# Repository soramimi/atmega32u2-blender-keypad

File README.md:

# atmega32u2-blender-keypad

Customized keypad for modeling with Blender.

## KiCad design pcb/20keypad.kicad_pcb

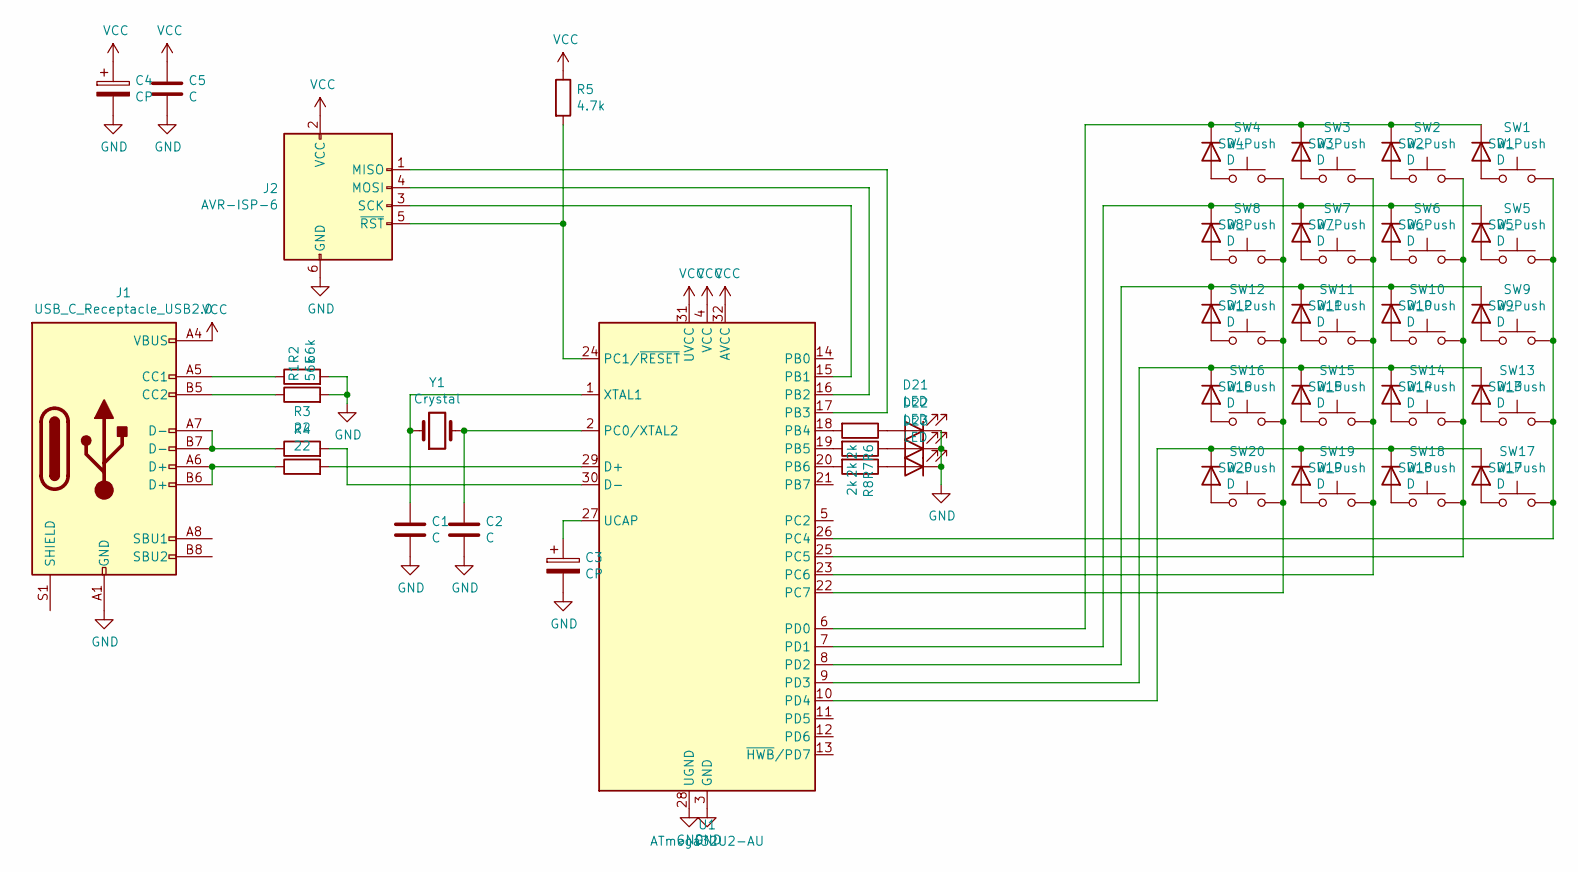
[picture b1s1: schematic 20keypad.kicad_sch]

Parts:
C1, C2, C5: C; C_Disc_D3.0mm_W1.6mm_P2.50mm
C3, C4: CP; CP_Radial_D6.3mm_P2.50mm
D1, D2, D3, D4, D5, D6, D7, D8, D9, D10, D11, D12, D13, D14, D15, D16, D17, D18, D19, D20: D; D_A-405_P7.62mm_Horizontal
D21, D22, D23: LED; LED_D3.0mm
J1: USB_C_Receptacle_USB2.0; USB_C_Receptacle_HRO_TYPE-C-31-M-12
J2: AVR-ISP-6; PinHeader_2x03_P2.54mm_Vertical
R1, R2: 56k; R_Axial_DIN0204_L3.6mm_D1.6mm_P2.54mm_Vertical
R3, R4: 22; R_Axial_DIN0204_L3.6mm_D1.6mm_P2.54mm_Vertical
R5: 4.7k; R_Axial_DIN0204_L3.6mm_D1.6mm_P2.54mm_Vertical
R6, R7, R8: 2k; R_Axial_DIN0204_L3.6mm_D1.6mm_P2.54mm_Vertical
SW1, SW2, SW3, SW4, SW5, SW6, SW7, SW8, SW9, SW10, SW11, SW12, SW13, SW14, SW15, SW16, SW17, SW18, SW19, SW20: SW_Push; SW_Cherry_MX_1.00u_PCB
U1: ATmega32U2-AU; TQFP-32_7x7mm_P0.8mm
Y1: Crystal; Crystal_HC49-U_Vertical

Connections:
GND: C1.2, C2.2, C3.2, C4.2, C5.2, D21.1 (K), D22.1 (K), D23.1 (K), J1.A1 (GND), J1.A12 (GND), J1.B1 (GND), J1.B12 (GND), J2.6 (GND), R1.2, R2.2, U1.3 (GND), U1.28 (UGND)
unnamed: C1.1, U1.1 (XTAL1), Y1.1
unnamed: C2.1, U1.2 (PC0/XTAL2), Y1.2
unnamed: C3.1, U1.27 (UCAP)
unnamed: D1.1 (K), D2.1 (K), D3.1 (K), D4.1 (K), U1.6 (PD0)
unnamed: D1.2 (A), SW1.1
unnamed: D2.2 (A), SW2.1
unnamed: D3.2 (A), SW3.1
unnamed: D4.2 (A), SW4.1
unnamed: D5.1 (K), D6.1 (K), D7.1 (K), D8.1 (K), U1.7 (PD1)
unnamed: D5.2 (A), SW5.1
unnamed: D6.2 (A), SW6.1
unnamed: D7.2 (A), SW7.1
unnamed: D8.2 (A), SW8.1
unnamed: D9.2 (A), SW9.1
unnamed: D9.1 (K), D10.1 (K), D11.1 (K), D12.1 (K), U1.8 (PD2)
unnamed: D10.2 (A), SW10.1
unnamed: D11.2 (A), SW11.1
unnamed: D12.2 (A), SW12.1
unnamed: D13.1 (K), D14.1 (K), D15.1 (K), D16.1 (K), U1.9 (PD3)
unnamed: D13.2 (A), SW13.1
unnamed: D14.2 (A), SW14.1
unnamed: D15.2 (A), SW15.1
unnamed: D16.2 (A), SW16.1
unnamed: D17.1 (K), D18.1 (K), D19.1 (K), D20.1 (K), U1.10 (PD4)
unnamed: D17.2 (A), SW17.1
unnamed: D18.2 (A), SW18.1
unnamed: D19.2 (A), SW19.1
unnamed: D20.2 (A), SW20.1
unnamed: D21.2 (A), R6.1
unnamed: D22.2 (A), R7.1
unnamed: D23.2 (A), R8.1
unnamed: J1.A5 (CC1), R2.1
unnamed: J1.A6 (D+), J1.B6 (D+), R4.1
unnamed: J1.A7 (D-), J1.B7 (D-), R3.1
unnamed: J1.B5 (CC2), R1.1
unnamed: J2.1 (MISO), U1.17 (PB3)
unnamed: J2.3 (SCK), U1.15 (PB1)
unnamed: J2.4 (MOSI), U1.16 (PB2)
unnamed: J2.5 (~RST), R5.2, U1.24 (PC1/~RESET)
unnamed: R3.2, U1.30 (D-)
unnamed: R4.2, U1.29 (D+)
unnamed: R6.2, U1.18 (PB4)
unnamed: R7.2, U1.19 (PB5)
unnamed: R8.2, U1.20 (PB6)
unnamed: SW1.2, SW5.2, SW9.2, SW13.2, SW17.2, U1.26 (PC4)
unnamed: SW2.2, SW6.2, SW10.2, SW14.2, SW18.2, U1.25 (PC5)
unnamed: SW3.2, SW7.2, SW11.2, SW15.2, SW19.2, U1.23 (PC6)
unnamed: SW4.2, SW8.2, SW12.2, SW16.2, SW20.2, U1.22 (PC7)
VCC: C4.1, C5.1, J1.A4 (VBUS), J1.A9 (VBUS), J1.B4 (VBUS), J1.B9 (VBUS), J2.2 (VCC), R5.1, U1.4 (VCC), U1.31 (UVCC), U1.32 (AVCC)

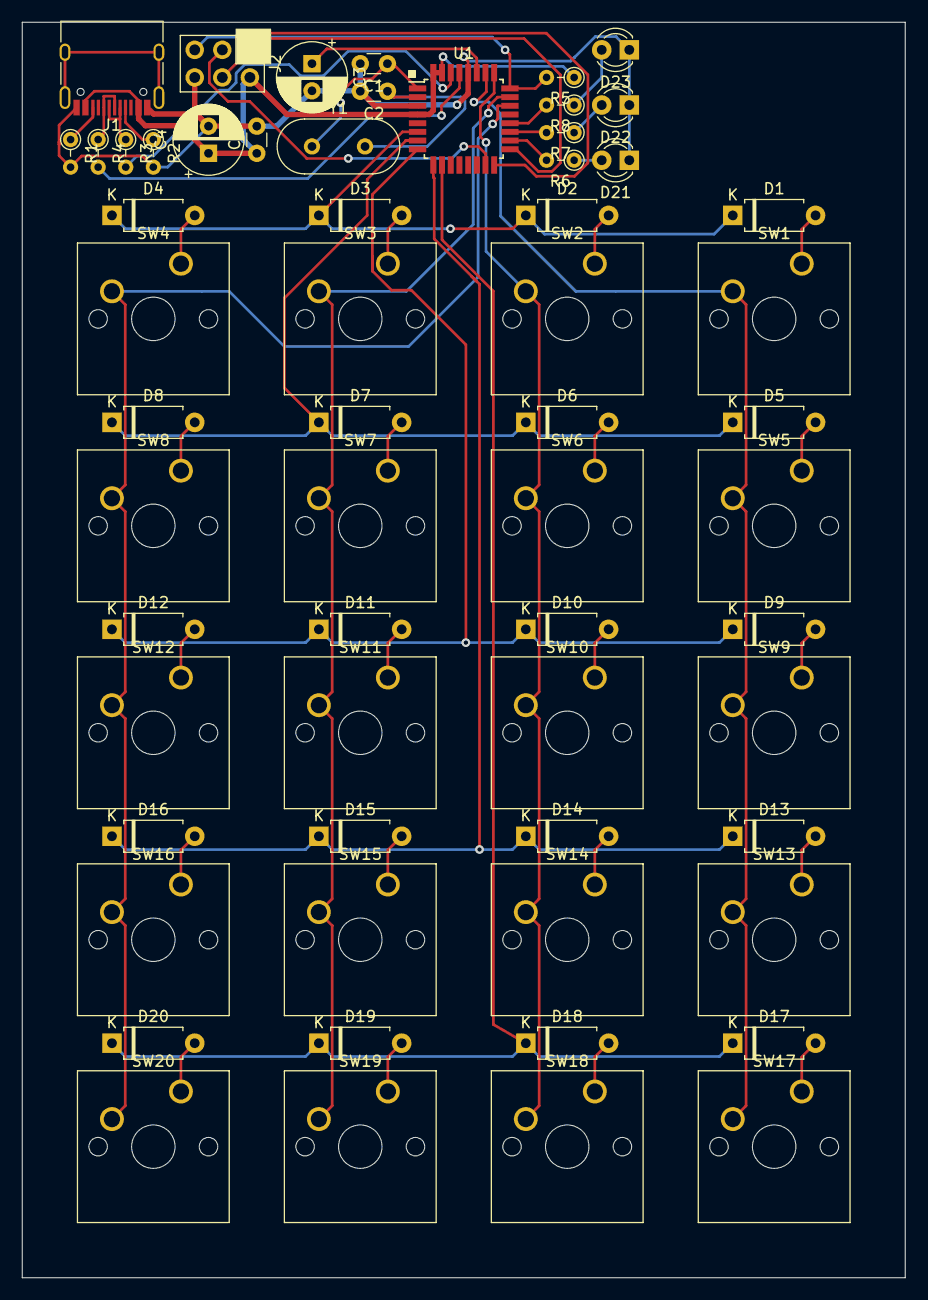
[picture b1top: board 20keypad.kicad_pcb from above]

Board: 2 copper layers, 81.3 x 115.6 mm, 60 parts (0 on the bottom side), 50 nets.

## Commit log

2022-01-01 first
2022-01-01 fix layout.png
2022-01-01 fix typo
2022-01-01 add case models
2022-01-01 update docs
2023-05-14 change layout
2023-05-27 fix extra modifier
2023-09-18 merge
2023-09-18 docs
2024-01-30 jp input mode
2024-01-30 fn key mode
